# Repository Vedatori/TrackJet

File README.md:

# TrackJet (cz)
TrackJet je otevřená platforma robotického vozidla vyvinutá pro [Robotický tábor 2021](http://wp.vedatori.com/pobytove-tabory/) organizovaný spolkem [Vědátoři](http://wp.vedatori.com/). Jedná se o nástupní verzi vozidla [TrackRay](https://github.com/vedatori/TrackRay), ve které byly vylepšeny jeho terénní schopnosti a přidány nové funkcionality. Byla redesignována mehanická konstrukce i řídicí elektronika, pro kterou byl vyvinut odpovídající software. 

Hlavní mechanickou částí je 3D tištěné šasi, které je doplněno dalšími 3D tištěnými díly. Plošné díly jsou laserem vyřezány z překližky. Spojování je prováděno především šrouby M3. Je použito minimum lepených spojů tak, aby bylo možné vrátit jakýkoliv krok při stavbě. Obsahuje zadní pohonná kola a na každé straně dále tři kola pro vedení pásu. Všechna kola jsou uložena pevně. Pásy jsou vytištěny na 3D tiskárně tak, aby se již při tisku vytvořilo kloubové spojení jednotlivých segmentů, což vede ke snížení času potřebného pro stavbu.

Veškerá elektronika je umístěna na jedné DPS. Ze spodní strany je připevněn zdroj energie - akumulátor 18650. Jeho nabíjení je řešeno na DPS, pro nabití není nutné ho vyjmout. Robota řídí ESP32 připájené přímo do DPS. Pro orientaci v prostoru robot využívá snímání pohybu pásů pomocí optických enkodérů a senzoru LiDAR umístěného na otočné konzoli. Vstupy od uživatele je možné zadat pomocí rotačního enkodéru, potenciometru a tlačítka, výstupy jsou zobrazeny na LED matici, bzučákem nebo jiných LED. Programování a nabíjení robota je prováděno přes USB-C.

Software je připraven na výuku programování. Tomu je přizpůsobena knihovna, pomocí které uživatelé jednoduše ovládají periferie robota bez nutnosti nízkoúrovňového programování jednotlivých částí. Pro výuku programování je připraven také návod popisující jednotlivé funkce a příklady jejich použití. Vše bylo navrženo s důrazem na rozvoj schopností algoritmizace a programování účastníků.
Součástí softwarového balíku je i kompletní program pro dálkové ovládání přes WiFi. Vozidlo umožňuje komunikaci jak přes vlastní WiFi, tak přihlášení k již existující síti. To mu umožňuje jízdu i v širém prostoru. TrackJet můžete vidět v akci v [tomto videu](https://www.youtube.com/watch?v=zHig3jCnhBY).

Při stavbě TrackJet postupujte podle připravených návodů v následujícím pořadí:
1. [Návod pro mechaniku](https://github.com/vedatori/TrackJet/blob/main/Manuals/TrackJet_mechanics_cz.md)
1. [Návod pro elektroniku](https://github.com/vedatori/TrackJet/blob/main/Manuals/TrackJet_electronics_cz.md)
1. [Návod pro programování](https://github.com/vedatori/TrackJet/blob/main/Manuals/TrackJet_programming_cz.md)

## Licence
* Obsah tohoto repozitáře mimo složku *Software* je sdílen pod licencí [Attribution-NonCommercial-ShareAlike 4.0 International (CC BY-NC-SA 4.0)](https://creativecommons.org/licenses/by-nc-sa/4.0/).
* Obsah složky *Software* je sdílen pod licencí [GNU Lesser General Public License v3.0](https://www.gnu.org/licenses/lgpl-3.0.en.html).

# TrackJet (en)

TrackJet is an open-source robotic vehicle platform developed for the [Robotic camp 2021 (cz)](http://wp.vedatori.com/pobytove-tabory/) organized by [Vědátoři (cz)](http://wp.vedatori.com/) society. It is a succesor of [TrackRay](https://github.com/vedatori/TrackRay) robotic vehicle. TrackJet introduces enhanced terrain abilities and new functionalities. Mechanical parts, electronics and software were redesigned.

TrackJet consists of a main 3D printed part - chassis, several other 3D printed parts and laser cut plywood parts. M3 bolts are used in the assembly process, which grants the possibility to undo every step in case of assembly error. Rear propulsion wheel and three guiding wheels are placed on every side of the vehicle. Tracks are designed to be 3D printed in one piece with joints between segments which minimizes assembly time.

All electronic components are placed on a single PCB. This board contains 18650 battery and a charger circuit. Therefore, it is not needed to take the battery out in order to charge it. ESP32 soldered to the PCB is used for peripherals control and WiFi connectivity. TrackJet finds its orientation in space using LiDAR sensor and optical encoders. User inputs can be made using rotary encoder, potentiometer and a button. LED matrix, buzzer and other LEDs are used for communication with user. Vehicle is programmed and charged via USB-C.

Electronics and software is designed for programming education. TrackJet contains a library which allows easy peripherals control without the need of low-level programming abilities. Repository contains programming manual (in czcech language) with description of commands and examples. WiFi remote control is a part of the software pack in this repository. ESP32 can be connected to external WiFi or it can create its own network so it is possible to drive outdoors without network coverage. You can see TrackJet in action in [this video](https://www.youtube.com/watch?v=zHig3jCnhBY).

In the build of the TrackJet proceed according to the prepared manuals in the following order:
1. [Mechanics manual](https://github.com/vedatori/TrackJet/blob/main/Manuals/TrackJet_mechanics_cz.md)
1. [Electronics manual](https://github.com/vedatori/TrackJet/blob/main/Manuals/TrackJet_electronics_cz.md)
1. [Programming manual](https://github.com/vedatori/TrackJet/blob/main/Manuals/TrackJet_programming_cz.md)

## License
* The contents of this repository excluding folder *Software* is shared under license [Attribution-NonCommercial-ShareAlike 4.0 International (CC BY-NC-SA 4.0)](https://creativecommons.org/licenses/by-nc-sa/4.0/).
* The contents of the folder *Software* is shared under license [GNU Lesser General Public License v3.0](https://www.gnu.org/licenses/lgpl-3.0.en.html).

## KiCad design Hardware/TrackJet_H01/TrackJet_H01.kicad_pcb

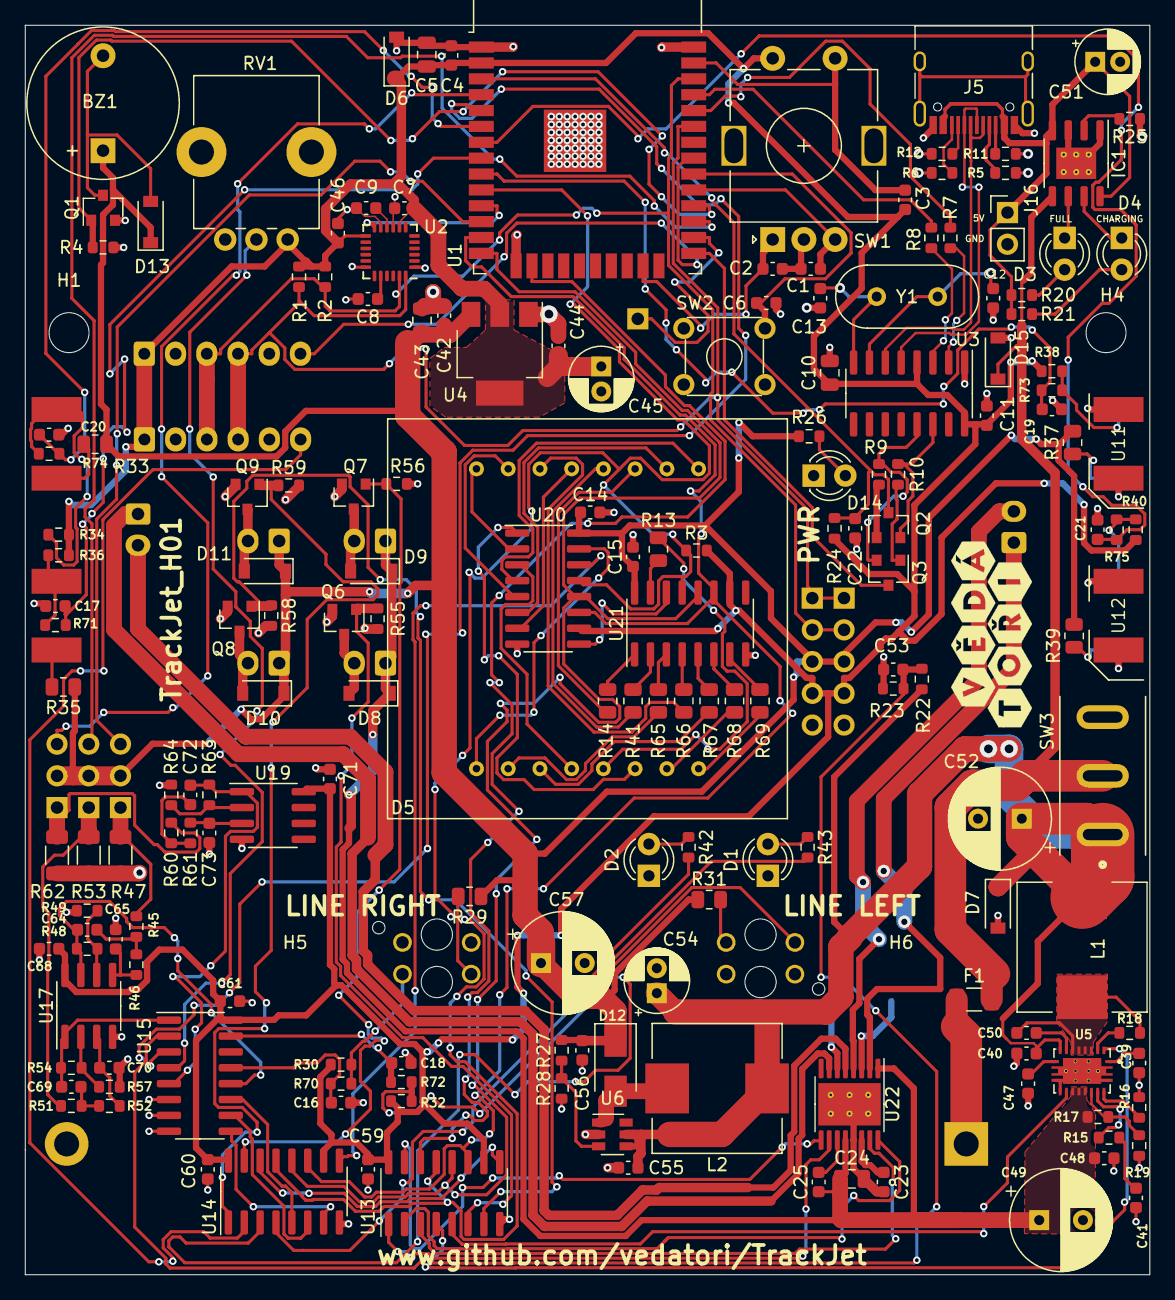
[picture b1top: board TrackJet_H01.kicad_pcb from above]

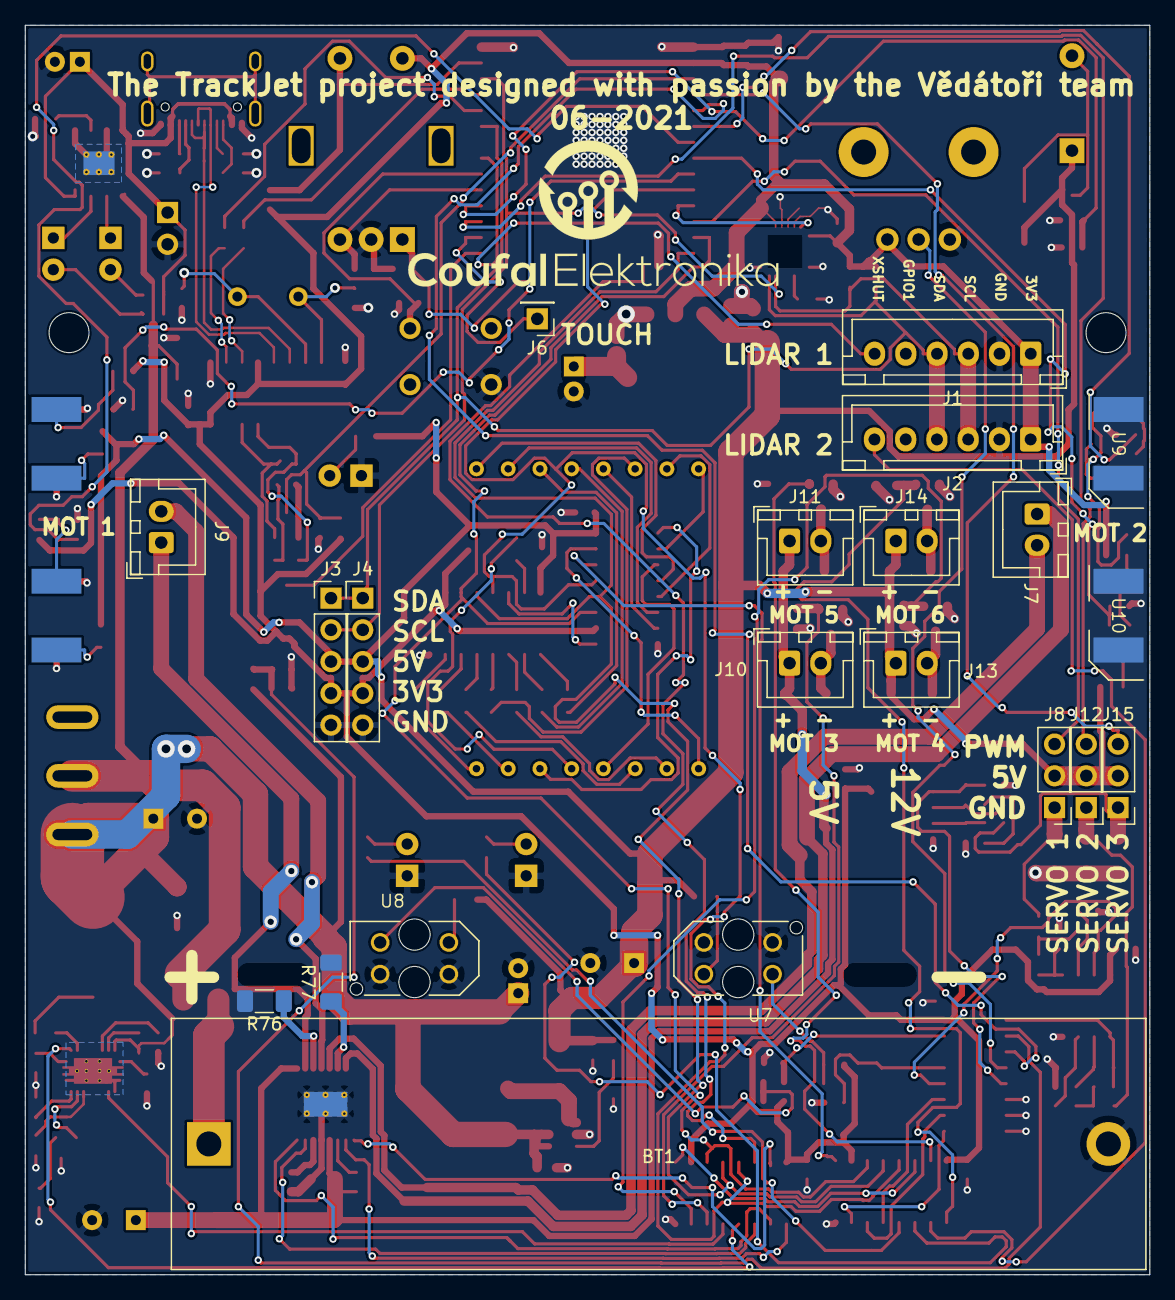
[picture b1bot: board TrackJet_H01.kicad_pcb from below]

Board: 2 copper layers, 90.0 x 100.0 mm, 205 parts (22 on the bottom side), 156 nets.

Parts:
BT1: 18650; BatteryHolder_MPD_BH-18650-PC2_NoHoles
BZ1: Buzzer; Buzzer_12x9.5RM7.6
C1, C2, C3, C4, C6, C7, C9, C11, C14, C15, C16, C17, C18, C19, C20, C21, C40, C42, C44, C46, C47, C48, C50, C53, C55, C56, C59, C60, C61, C68, C71: 100n; C_0603_1608Metric
C5, C10, C24, C43: 10u; C_0805_2012Metric
C8: 2n2; C_0603_1608Metric
C12, C13: 22p; C_0603_1608Metric
C22, C39: 1u; C_0603_1608Metric
C23: 2u2; C_0603_1608Metric
C25: 10n; C_0603_1608Metric
C41: 1n; C_0603_1608Metric
C45, C51, C54: 100u; CP_Radial_D5.0mm_P2.00mm
C49, C52, C57: 1000u 16V; CP_Radial_D8.0mm_P3.50mm
C64, C65, C69, C70, C72, C73: 220n; C_0603_1608Metric
D1, D2: LED; LED_D3.0mm
D3, D14: LED_GREEN; LED_D3.0mm
D4: LED_RED; LED_D3.0mm
D5: KYX-1088AS
D6, D7, D8, D9, D10, D11, D13, D15: B5819W; D_SOD-123
D12: SS34; D_SMA
F1: Fuse 15A; Fuse_1206_3216Metric
G1: LOGO; Coufal_elektronika_text_30x13mm
G2: LOGO; Vedatori_15mm
H1, H4: MountingHole; MountingHole_3.2mm_M3
H5, H6: MountingHole; ZIP_Tie_Slot_Hole
IC1: TP4056; SOIC-8-1EP_3.9x4.9mm_P1.27mm_EP2.514x3.2mm_ThermalVias
J1, J2: Conn_01x06_Female; JST_XH_B6B-XH-A_1x06_P2.50mm_Vertical
J3, J4: Conn_01x05_Male; PinHeader_1x05_P2.54mm_Vertical
J5: TYPE-C-31-M-12; USB_C_Receptacle_HRO_TYPE-C-31-M-12
J6: Conn_01x01_Male; PinHeader_1x01_P2.54mm_Vertical
J7, J9, J10, J11, J13, J14: Conn_01x02; JST_XH_B2B-XH-A_1x02_P2.50mm_Vertical
J8, J12, J15: Conn_01x03_Male; PinHeader_1x03_P2.54mm_Vertical
J16: Conn_01x02_Male; PinHeader_1x02_P2.54mm_Vertical
L1: 2u2; L_Wuerth_HCI-1040
L2: 22uH; L_Wuerth_HCI-1040
Q1: 2N7002; SOT-23
Q2, Q3: S8050; SOT-23
Q6, Q7, Q8, Q9: AO3400A; SOT-23
R1, R2: 2K2; R_0603_1608Metric
R3, R4, R24, R55, R56, R58, R59: 10K; R_0603_1608Metric
R5, R6, R11, R12: 5K1; R_0603_1608Metric
R7, R8: 470R; R_0603_1608Metric
R9, R10: 12K; R_0603_1608Metric
R13, R14, R29, R31, R33, R35, R37, R39, R41, R65, R66, R67, R68, R69: 100R; R_0805_2012Metric
R15: 24K; R_0603_1608Metric
R16: 150K; R_0603_1608Metric
R17: 200K; R_0603_1608Metric
R18: 240K; R_0603_1608Metric
R19, R28: 30K; R_0603_1608Metric
R20, R21, R26, R30, R32, R34, R36, R38, R40: 1K; R_0603_1608Metric
R22, R46, R52, R61: 1M; R_0603_1608Metric
R23: 3M; R_0603_1608Metric
R25: 1K2; R_0603_1608Metric
R27: 220K; R_0603_1608Metric
R42, R43: 220R; R_0603_1608Metric
R45, R51, R60, R70, R71, R72, R73, R74, R75: 22K; R_0603_1608Metric
R47, R53, R62: 0R1; R_1206_3216Metric
R48, R54, R63: 47K; R_0603_1608Metric
R49, R57, R64: 1K5; R_0603_1608Metric
R76, R77: R; R_1206_3216Metric_Pad1.30x1.75mm_HandSolder
RV1: R_POT; Potentiometer_Alps_RK09K_Single_Vertical
SW1: Rotary_Encoder_Switch; RotaryEncoder_Alps_EC11E-Switch_Vertical_H20mm
SW2: SW_DPST; SW_TH_Tactile_Omron_B3F-10xx
SW3: MT-102; TE_A101SYCQ04
U1: ESP32-WROOM-32D; ESP32-WROOM-32
U2: MPU-6050; InvenSense_QFN-24_4x4mm_P0.5mm
U3: CH340G; SOIC-16_3.9x9.9mm_P1.27mm
U4: AMS1117-3.3; SOT-223-3_TabPin2
U5: TPS61088RHLR; IC_TPS61088RHLR
U6: MT3608; SOT-23-6
U7, U8: TCRT5000
U9, U10, U11, U12: TCRT5000; TCRT5000_SMD
U13, U14, U20, U21: 74HC595; SOIC-16_3.9x9.9mm_P1.27mm
U15: CD4051B; SOIC-16_3.9x9.9mm_P1.27mm
U17, U19: LM358; SOIC-8_3.9x4.9mm_P1.27mm
U22: DRV8833PWP; HTSSOP-16-1EP_4.4x5mm_P0.65mm_EP3.4x5mm_Mask2.46x2.31mm_The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
Y1: 12MHz; Crystal_HC49-4H_Vertical

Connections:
+3V3: C3.2, C4.1, C5.1, C7.1, C10.1, C11.1, C44.1, C45.1, C46.1, C59.1, C60.1, C61.1, C68.1, C71.1, D6.1, J1.1, J2.1, J3.4, J4.4, R1.1, R2.1, R3.1, R24.1, R30.1, R32.1, R34.1, R36.1, R38.1, R40.1, RV1.1, SW1.S2, U1.2, U2.8, U2.13, U3.4, U3.16, U4.2, U13.10, U13.16, U14.10, U14.16, U15.16, U17.8, U19.8, U20.10, U21.10
+5V: BZ1.1, C14.1, C15.1, C42.1, C43.1, C56.1, C57.1, D10.1, D11.1, D12.1, D13.1, J3.3, J4.3, J8.2, J12.2, J13.1, J14.1, J15.2, R26.1, R27.2, R29.1, R31.1, R33.1, R35.1, R37.1, R39.1, U4.3, U20.16, U21.16
+5VP: C51.1, IC1.4, IC1.8, J5.A4, J5.A9, J5.B4, J5.B9, J16.1, R20.1, R21.1
+12V: C24.1, C25.1, C48.1, C49.1, D8.1, D9.1, J10.1, J11.1, R17.2, U5.14, U5.15, U5.16, U22.1, U22.12
+BATT: C40.1, C52.1, C54.1, C55.1, D7.1, L1.1, L2.1, R22.1, SW3.1, U5.9, U6.4, U6.5
/Encoders/ENCODER2: C17.1, R71.1, U1.8
/Encoders/ENCODER4: C19.1, R73.1, U1.9
/Encoders/ENCODER5: C20.1, R74.1, U1.6
/Encoders/ENCODER6: C21.1, R75.1, U1.7
/Gyro/MPU-6050_INT: U1.11, U2.12
/Motors/DC_MOT1_12V: Q6.1, R55.1, U13.6
/Motors/DC_MOT2_5V: Q8.1, R58.1, U13.7
/Motors/DC_MOT3_12V: Q7.1, R56.1, U14.15
/Motors/DC_MOT4_5V: Q9.1, R59.1, U14.1
/Motors/MOTA_IN1: U13.15, U22.9
/Motors/MOTA_IN2: U13.1, U22.10
/Motors/MOTB_IN1: U13.2, U22.16
/Motors/MOTB_IN2: U13.3, U22.15
/Motors/SERVO1_CTRL: J8.3, U1.12
/Motors/SERVO2_CTRL: J12.3, U1.27
/Motors/SERVO3_CTRL: J15.3, U1.4
/Mux Demux Matrix/Analog_IN_1: C16.1, R70.1, U15.13
/Mux Demux Matrix/Analog_IN_3: C18.1, R72.1, U15.15
/Mux Demux Matrix/Analog_IN_4: C64.1, R48.1, U15.12, U17.7
/Mux Demux Matrix/Analog_IN_5: C69.1, R54.1, U15.1, U17.1
/Mux Demux Matrix/Analog_IN_6: C72.1, R63.1, U15.5, U19.1
/Mux Demux Matrix/Analog_IN_7: C53.1, R22.2, R23.1, U15.2
/Mux Demux Matrix/Analog_MUX: U1.5, U15.3
/Mux Demux Matrix/REG_CLK: U1.13, U13.11, U14.11, U20.11, U21.11
/Mux Demux Matrix/REG_DAT: U1.16, U13.14
/Mux Demux Matrix/REG_LAT: U1.14, U13.12, U14.12, U20.12, U21.12
/Mux Demux Matrix/REG_OE: R3.2, U1.10, U13.13, U14.13, U20.13, U21.13
/Mux Demux Matrix/REG_OUT_11: J2.6, U14.2
/Power/12V_ENABLE: U5.2, U13.4
/Power/12V_MODE: U5.13, U13.5
/USB/D+: J5.A6, J5.B6, U3.5
/USB/D-: J5.A7, J5.B7, U3.6
/USB/ESP_GPIO0: Q3.3, U1.25
/USB/ESP_RST: C22.2, Q2.3, R24.2, U1.3
/USB/ESP_RX: R7.1, U1.34
/USB/ESP_TX: R8.1, U1.35
BUTTON: C6.2, SW2.2, U1.30
BUZZER: Q1.1, R4.1, U1.28
ENC_A: C2.1, SW1.A, U1.23
ENC_B: C1.2, SW1.B, U1.29
ENC_SW: C3.1, SW1.S1, U1.37
GND: BT1.2, C1.1, C2.2, C4.2, C5.2, C6.1, C7.2, C8.2, C9.2, C10.2, C11.2, C12.2, C13.2, C14.2, C15.2, C16.2, C17.2, C18.2, C19.2, C20.2, C21.2, C22.1, C23.2, C24.2, C39.1, C40.2, C41.1, C42.2, C43.2, C44.2, C45.2, C46.2, C47.2, C48.2, C49.2, C51.2, C52.2, C53.2, C54.2, C55.2, C56.2, C57.2, C59.2, C60.2, C61.2, C65.1, C68.2, C70.1, C71.2, C73.1, D1.1, D2.1, D6.2, D7.2, D14.1, D15.2, IC1.1, IC1.3, IC1.9, J1.2, J2.2, J3.5, J4.5, J5.A1, J5.A12, J5.B1, J5.B12, J16.2, Q1.2, Q6.2, Q7.2, Q8.2, Q9.2, R4.2, R5.1, R6.1, R11.2, R12.2, R16.1, R19.1, R23.2, R25.1, R28.1, R47.2, R49.1, R53.2, R55.2, R56.2, R57.1, R58.2, R59.2, R62.2, R64.1, R76.2, R77.2, RV1.3, SW1.C, SW2.3, U1.1, U1.15, U1.38, U1.39, U2.1, U2.9, U2.11, U2.18, U3.1, U4.1, U5.11, U5.12, U5.20, U5.21, U5.22, U5.23, U5.24, U5.25, U5.26, U5.27, U5.28, U5.29, U6.2, U7.2, U7.4, U8.2, U8.4, U9.2, U9.4, U10.2, U10.4, U11.2, U11.4, U12.2, U12.4, U13.8, U14.8, U15.6, U15.7, U15.8, U17.4, U19.4, U20.8, U21.8, U22.13, U22.17
unnamed: BT1.1, F1.2
unnamed: BZ1.2, D13.2, Q1.3
unnamed: C8.1, U2.20
unnamed: C9.1, U2.10
unnamed: C12.1, U3.7, Y1.1
unnamed: C13.1, U3.8, Y1.2
unnamed: C23.1, U22.14
unnamed: C25.2, U22.11
unnamed: C39.2, U5.1
unnamed: C41.2, R15.1
unnamed: C47.1, U5.10
unnamed: C50.1, U5.8
unnamed: C50.2, L1.2, R18.2, U5.4, U5.5, U5.6, U5.7
unnamed: C64.2, R45.1, R46.2
unnamed: C65.2, R46.1, U17.5
unnamed: C69.2, R51.1, R52.2
unnamed: C70.2, R52.1, U17.3
unnamed: C72.2, R60.1, R61.2
unnamed: C73.2, R61.1, U19.3
unnamed: D1.2, R43.1
unnamed: D2.2, R42.1
unnamed: D3.1, IC1.6
unnamed: D3.2, R20.2
unnamed: D4.1, IC1.7
unnamed: D4.2, R21.2
unnamed: D5.1, U20.4
unnamed: D5.2, U20.6
unnamed: D5.3, R14.2
unnamed: D5.4, R41.2
unnamed: D5.5, U20.7
unnamed: D5.6, R66.2
unnamed: D5.7, U20.5
unnamed: D5.8, U20.2
unnamed: D5.9, U20.15
unnamed: D5.10, R65.2
unnamed: D5.11, R67.2
unnamed: D5.12, U20.3
unnamed: D5.13, R13.2
unnamed: D5.14, U20.1
unnamed: D5.15, R68.2
unnamed: D5.16, R69.2
unnamed: D8.2, J10.2, Q6.3
unnamed: D9.2, J11.2, Q7.3
unnamed: D10.2, J13.2, Q8.3
unnamed: D11.2, J14.2, Q9.3
unnamed: D12.2, L2.2, U6.1
unnamed: D14.2, R26.2
unnamed: D15.1, F1.1, IC1.5, SW3.2
unnamed: IC1.2, R25.2
unnamed: J1.6, U1.31
unnamed: J5.A5, R5.2
unnamed: J5.A8, R12.1
unnamed: J5.B5, R6.2
unnamed: J5.B8, R11.1
unnamed: J6.1, U1.26
unnamed: J7.1, U22.7
unnamed: J7.2, U22.5
unnamed: J8.1, R45.2, R47.1
unnamed: J9.1, U22.2
unnamed: J9.2, U22.4
unnamed: J12.1, R51.2, R53.1
unnamed: J15.1, R60.2, R62.1
unnamed: Q2.1, R9.1
unnamed: Q2.2, R10.2, U3.14
unnamed: Q3.1, R10.1
unnamed: Q3.2, R9.2, U3.13
unnamed: R7.2, U3.2
unnamed: R8.2, U3.3
unnamed: R13.1, U21.15
unnamed: R14.1, U21.1
unnamed: R15.2, U5.18
unnamed: R16.2, U5.19
unnamed: R17.1, R19.2, U5.17
unnamed: R18.1, U5.3
unnamed: R27.1, R28.2, U6.3
unnamed: R29.2, U7.1
unnamed: R30.2, R70.2, U7.3
unnamed: R31.2, U8.1
unnamed: R32.2, R72.2, U8.3
unnamed: R33.2, U9.1
unnamed: R34.2, R74.2, U9.3
unnamed: R35.2, U10.1
unnamed: R36.2, R71.2, U10.3
unnamed: R37.2, U11.1
unnamed: R38.2, R73.2, U11.3
unnamed: R39.2, U12.1
unnamed: R40.2, R75.2, U12.3
unnamed: R41.1, U21.2
unnamed: R42.2, U14.3
unnamed: R43.2, U14.4
unnamed: R48.2, R49.2, U17.6
unnamed: R54.2, R57.2, U17.2
unnamed: R63.2, R64.2, U19.2
unnamed: R65.1, U21.3
unnamed: R66.1, U21.4
unnamed: R67.1, U21.5
unnamed: R68.1, U21.6
unnamed: R69.1, U21.7
unnamed: R76.1, U22.3
unnamed: R77.1, U22.6
unnamed: U13.9, U14.14
unnamed: U14.5, U15.11
unnamed: U14.6, U15.10
unnamed: U14.7, U15.9
unnamed: U14.9, U20.14
unnamed: U20.9, U21.14
POT: RV1.2, U15.4
SCL: J1.3, J2.3, J3.2, J4.2, R2.2, U1.36, U2.23
SDA: J1.4, J2.4, J3.1, J4.1, R1.2, U1.33, U2.24

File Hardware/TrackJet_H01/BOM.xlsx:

Comment | Designator | Footprint | LCSC
22p | C12,C13 | Capacitor_SMD:C_0603_1608Metric | C1653
1u | C22,C39 | Capacitor_SMD:C_0603_1608Metric | C15849
2u2 | C23 | Capacitor_SMD:C_0603_1608Metric | C23630
10n | C25 | Capacitor_SMD:C_0603_1608Metric | C57112
100n | C1,C2,C3,C4,C6,C7,C9,C11,C14,C15,C16,C17,C18,C19,C20,C21,C40,C42,C44,C46,C47,C4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 | Capacitor_SMD:C_0603_1608Metric | C14663
1n | C41 | Capacitor_SMD:C_0603_1608Metric | C1588
10u | C5,C10,C24,C43 | Capacitor_SMD:C_0805_2012Metric | C15850
220n | C64,C65,C69,C70,C72,C73 | Capacitor_SMD:C_0603_1608Metric | C21120
2n2 | C8 | Capacitor_SMD:C_0603_1608Metric | C1604
SS34 | D12 | Diode_SMD:D_SMA | C8678
B5819W | D6,D7,D8,D9,D10,D11,D13,D15 | Diode_SMD:D_SOD-123 | C8598
Fuse 15A | F1 | Fuse:Fuse_1206_3216Metric | C182976
TP4056 | IC1 | Package_SO:SOIC-8-1EP_3.9x4.9mm_P1.27mm_EP2.514x3.2mm_ThermalVias | C382139
TYPE-C-31-M-12 | J5 | Connector_USB:USB_C_Receptacle_HRO_TYPE-C-31-M-12 | C165948
2u2 | L1 | Inductor_SMD:L_Wuerth_HCI-1040 | C149550
22uH | L2 | Inductor_SMD:L_Wuerth_HCI-1040 | C182173
2N7002 | Q1 | Package_TO_SOT_SMD:SOT-23 | C8545
S8050 | Q2,Q3 | Package_TO_SOT_SMD:SOT-23 | C2146
AO3400A | Q6,Q7,Q8,Q9 | Package_TO_SOT_SMD:SOT-23 | C20917
12K | R9,R10 | Resistor_SMD:R_0603_1608Metric | C22790
5K1 | R5,R6,R11,R12 | Resistor_SMD:R_0603_1608Metric | C23186
24K | R15 | Resistor_SMD:R_0603_1608Metric | C23352
150K | R16 | Resistor_SMD:R_0603_1608Metric | C22807
200K | R17 | Resistor_SMD:R_0603_1608Metric | C25811
240K | R18 | Resistor_SMD:R_0603_1608Metric | C4197
30K | R19,R28 | Resistor_SMD:R_0603_1608Metric | C22984
2K2 | R1,R2 | Resistor_SMD:R_0603_1608Metric | C4190
1K | R20,R21,R26,R30,R32,R34,R36,R38,R40 | Resistor_SMD:R_0603_1608Metric | C21190
1M | R22,R46,R52,R61 | Resistor_SMD:R_0603_1608Metric | C22935
3M | R23 | Resistor_SMD:R_0603_1608Metric | C23156
1K2 | R25 | Resistor_SMD:R_0603_1608Metric | C22765
220K | R27 | Resistor_SMD:R_0603_1608Metric | C22961
100R | R13,R14,R29,R31,R33,R35,R37,R39,R41,R65,R66,R67,R68,R69 | Resistor_SMD:R_0805_2012Metric | C17408
10K | R3,R4,R24,R55,R56,R58,R59 | Resistor_SMD:R_0603_1608Metric | C25804
220R | R42,R43 | Resistor_SMD:R_0603_1608Metric | C22962
0R1 | R47,R53,R62 | Resistor_SMD:R_1206_3216Metric | C25334
47K | R48,R54,R63 | Resistor_SMD:R_0603_1608Metric | C25819
1K5 | R49,R57,R64 | Resistor_SMD:R_0603_1608Metric | C22843
22K | R45,R51,R60,R70,R71,R72,R73,R74,R75 | Resistor_SMD:R_0603_1608Metric | C31850
470R | R7,R8 | Resistor_SMD:R_0603_1608Metric | C23179
ESP32-WROOM-32D | U1 | RF_Module:ESP32-WROOM-32 | C473012
74HC595 | U13,U14,U20,U21 | Package_SO:SOIC-16_3.9x9.9mm_P1.27mm | C5947
CD4051B | U15 | Package_SO:SOIC-16_3.9x9.9mm_P1.27mm | C21379
LM358 | U17,U19 | Package_SO:SOIC-8_3.9x4.9mm_P1.27mm | C7950
MPU-6050 | U2 | Sensor_Motion:InvenSense_QFN-24_4x4mm_P0.5mm | C24112
CH340G | U3 | Package_SO:SOIC-16_3.9x9.9mm_P1.27mm | C14267
AMS1117-3.3 | U4 | Package_TO_SOT_SMD:SOT-223-3_TabPin2 | C6186
TPS61088RHLR | U5 | Sergej_Library:IC_TPS61088RHLR | C87357
MT3608 | U6 | Package_TO_SOT_SMD:SOT-23-6 | C84817

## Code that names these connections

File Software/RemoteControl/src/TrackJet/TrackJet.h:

#pragma once

#include <Arduino.h>
#include <Wire.h>
#include "Preferences.h"

#include "VL53L0X.h"
#include "MPU6050_light.h"

#include "SerialPWM.h"
#include "WiFiCaptain.h"
#include "QuadEncoder.h"
#include "SemiIntelligentServo.h"
#include "Music.h"


namespace TJ {

const uint16_t PWM_FREQUENCY = 1000;

const uint8_t REG_DAT = 13;
const uint8_t REG_CLK = 14;
const uint8_t REG_LATCH = 12;
const uint8_t REG_OE = 25;
const uint8_t I2C_SDA = 21;
const uint8_t I2C_SCL = 22;

const uint8_t ENC_A = 15;
const uint8_t ENC_B = 5;
const uint8_t ENC_SW = 23;
const uint8_t BUTTON = 18;
const uint8_t LIDAR = 19;
const uint8_t BUZZER = 17;
const uint8_t ADC_MUX = 39;
const adc1_channel_t ADC_CH_COM = ADC1_CHANNEL_3;
const adc1_channel_t ADC_CH_ENC_FR = ADC1_CHANNEL_4;
const adc1_channel_t ADC_CH_ENC_RL = ADC1_CHANNEL_5;
const adc1_channel_t ADC_CH_ENC_RR = ADC1_CHANNEL_6;
const adc1_channel_t ADC_CH_ENC_FL = ADC1_CHANNEL_7;

#define SERVO_COUNT 3
const uint8_t SERVO[SERVO_COUNT] = {27, 16, 36};
const uint8_t SERVO_CHANNEL[SERVO_COUNT] = {0, 1, 2};
const uint8_t BUZZER_CHANNEL = 3;

const float MOTOR_SPEED_FILTER_UPDATE_COEF = 0.15;
const float BATT_VOLTAGE_UPDATE_COEF = 0.05;
const float BATT_VOLTAGE_CUTOFF = 3.4;    // [V]
const float BATT_VOLTAGE_RESET = 3.6;     // [V]

const uint16_t encThresholdInit = 1600;

const uint8_t FREQ_PWM_THRESHOLD = 40;
const uint16_t controlPeriod = 10;  // [ms]
const char STORAGE_NAMESPACE[] = "TrackJet";
const uint16_t communicationTimeout = 1000;
const uint16_t lettersSwapTimeout = 500;
const uint16_t lettersBlankTimeout = 50;
const uint16_t lettersSweepTimeout =  100;

extern SerialPWM serialPWM;
extern QuadEncoder quadEnc;
extern SemiIntelligentServo servo[SERVO_COUNT];
extern MPU6050 mpu;
extern VL53L0X lidar;
void updatePWM(void * param);
void updateEnc(void * param);
uint8_t encGetState(uint8_t encID);
void handleRot();
void handleSW();
}

enum shiftRegPins {
    MOT1A, MOT1B, MOT2A, MOT2B, STEP_EN, STEP_MODE, MOT3, MOT4, MOT5, MOT6, 
    XSHUT, LED2, LED1, MUXA, MUXB, MUXC
};

enum adcMuxPins {
    LINE_SENSOR_RIGHT, NC, LINE_SENSOR_LEFT, SERVO_CURR_1, SERVO_CURR_2, SERVO_CURR_3, BAT_VOLT, POTENTIOMETER
};

class TrackJetClass {
    bool beginCalled = false;
    int8_t motorsSpeed[2];
    //float motorsSpeedFiltered[2];
    uint8_t gyroStatus = 0; // 0-disabled, 1-running, 2-calibrating
    float gyroYPR[3];
    float gyroOffsets[3];
    float accelOffsets[3];
    uint16_t analogReadData[8];
    uint8_t lidarStatus = 0;    // 0-disabled, 1-running
    uint16_t lidarDist = 0;
    Preferences preferences;
    uint32_t prevCommunicationTime = 0;
    bool connectionEnabled = false;
    bool connectionActive = false;
    String displayTextBuffer;
    float battVoltageFiltered = 3.7;
    float battPercentFiltered = 50;
    bool battCutoff = false;    // false-high V., true-low V.

    bool melodyPlaying = false;
    bool melodyPause = false;
    int melodyTempo = 180;
    const int * melody;
    int melodythisNote = 0;
    int melodySize = 0;
    unsigned long melodyLastMillis = 0;

public:
    uint16_t encThreshold[4];   // 0-FL, 1-RL, 2-FR, 3-RR
    int16_t encSteps[2];    // 0-Left, 1-right
    TrackJetClass();
    void begin();

    bool buttonRead();
    uint16_t potentiometerRead();   // 0-100
    bool encoderReadButton();
    bool encoderReadButtonPulse();
    int16_t encoderRead();
    void encoderReset();

    void motorSetSpeed(const int8_t index, int8_t speed);
    void motorsUpdateSpeed();
    void controlMovement(const int8_t joystickX, const int8_t joystickY);

    int16_t encoderGetSteps(uint8_t encID);
    float encoderGetDistance(uint8_t encID);
    float encoderGetSpeed(uint8_t encID);
    void encoderDistReset(uint8_t encID);

    void servoSetPosition(uint8_t servoID, float position);     // servoID 1, 2, 3; position 0-180 [°]
    void servoSetSpeed(uint8_t servoID, float speed);    // speed 0-600 [°/s]
    float servoGetPosition(uint8_t servoID);
    bool servoMoving(uint8_t servoID);

    void soundTone(float freq = 1000);
    void soundEnd();
    void playMelody(const int * aMelody, const int size, const int tempo = 180);
    void stopMelody();
    void handleMelody();

    uint8_t gyroGetStatus();
    float gyroAngleYPR(uint8_t index) ;
    void gyroCalibrate();
    void gyroUpdate();
    void printOffsets() {
        printf("offsets: %f %f %f %f %f %f\n", gyroOffsets[0], gyroOffsets[1], gyroOffsets[2], accelOffsets[0], accelOffsets[1], accelOffsets[2]);
    }

    void updateAnalogMux();

    float battVolt();
    float battPercentCalc(float voltage);
    uint8_t battPercent();
    void handleLowBatt();

    uint16_t lineRead(uint8_t index);

    uint16_t lidarDistance();
    void lidarUpdate();

    void ledWrite(uint8_t id, bool state);
    void ledWriteAnalog(uint8_t id, uint8_t brightness);    // brightness 0-100

    void displaySingle(uint8_t row, uint8_t col, bool state);
    void displaySingleAnalog(uint8_t row, uint8_t col, int8_t brightness);   // brightness 0-12
    void displayAll(int8_t value);
    void display(uint8_t state[][DISP_COLS]);
    void displayDigit(const uint8_t digit);
    void displayChar(const char letter, int8_t sweepRight = 0, int8_t sweepDown = 0);
    void displayText(String text = "", bool sweep = true);
    bool displayIsBusy();

    void startWiFiCaptain(String name="", String password="");
    void checkConnection();
    String commandGet();
    String commandGetIndexed(uint8_t index);
    void commandClear();
    void internCommandHandle();
    void commandSend(String type, String text);
    void commandDisp(String text);
    void sendStatus();

    void encoderCalibrate(uint16_t duration);
};

extern TrackJetClass TrackJet;

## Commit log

2021-03-19 Initial commit. Repository upgrade.
2021-03-19 Added first Hardware prototype.
2021-03-22 Routed PCB
2021-03-23 Final changes made to Sergej_H00, exported gerbers
2021-03-23 updated schematics - part values and LCSC numbers
2021-04-22 Notes for H01 and electronics analysis.
2021-04-29 To do list for next HW version
2021-04-29 exported layout in PDF
2021-05-02 Started testing I2S parallel
2021-05-07 Removed "data pins" universality
2021-05-08 Functional remote control demo.
2021-05-14 Removed [ ] pwm operator.
2021-05-15 ShiftReg pin mapping and Handling OE pin in class.
2021-05-16 removed std_vector and initializer list, output indexing from 0
2021-05-17 Displaying any matrix setting defined in 2d array
2021-05-17 Fixed diplay orientation. Simple serialPWM disp api.
2021-05-17 Adding disp api array bound security.
2021-05-17 Renamed everywhere to TrackJet.
2021-05-17 Integrated SerialPWM into RemoteControl.
2021-05-18 Rotated disp orientation to be viewed from front. Displaying texts.
2021-05-18 Added quadratic encoder.
2021-05-19 Refactoring TJ function names, shift reg output pins ordering.
2021-05-22 Controlling servos (+remotely through commands).
2021-05-22 Created TrackJet_H01
    Created TrackJet_H01 KiCad project and ported H00 version. Updated To-Do list. Renamed all files to TrackJet_Hxx except Sergej Library for compatibiliti with used symbols and footprints.
2021-05-22 Introduced servo class.
2021-05-22 Added speed adjustment of servos.
2021-05-23 Added MPU6050_light and reading YPR, calibrating and storing gyro calibration.
2021-05-23 Indicating tilt angles on display.
2021-05-23 Storing accelerometer calibration.
2021-05-24 Added lidar.
2021-05-29 Reading analog from mux in single-connection mode.
2021-06-11 Updated H01 PCB
2021-06-13 Updated H01
2021-06-13 Lidar measurements with defined period
2021-06-14 H01 update
2021-06-14 Exported H01 manufactuirng data
2021-06-14 Updated manufacturing data
2021-07-11 Transition to H01. Added tracks encoder demo. Remove servo steady movement because of a bug.
2021-07-30 Mechanics manual cz, 1st version
2021-07-31 Mechanics manual cz, revision
2021-08-08 Fixed lib naming issues with mac. Pinned updatePWM task to core 1 (same as main)
2021-08-08 Review návodu pro mechaniku.
2021-08-08 Fixed WiFi softAp name conflict. Removed default password.
2021-08-10 Electronics manual cz, 1st version
2021-08-10 Electronics manual cz, revision
2021-08-10 Reading analog mux inputs. Monitoring battery voltage.
2021-08-10 Gyro preferences loading only when gyro connected.
2021-08-11 programing manual init
2021-08-11 Prog.manual update till "new project"
2021-08-12 Handling intern control commands (reset).
2021-08-12 Fixed servo linear movement
2021-08-12 Added buzzer functions
2021-08-12 Fixed servo commands calling. Added command entry autofocus.
2021-08-12 Mechanics manual, cz, revision
2021-08-12 Updated API for LED control. Prog.manual till buttons.
2021-08-12 Electronics manual review
2021-08-12 Added second encoder monitoring.
2021-08-12 Encoder calibration
2021-08-13 Manual electronics cz, review
2021-08-13 Small fixes
2021-08-13 Manual electronics edit
2021-08-13 Updated structure of programming manual.
2021-08-13 First 2 prog. lectures
2021-08-13 More programming lectures
2021-08-14 programming lectures update
    button
2021-08-14 Mechanics manual minor fix
2021-08-14 Fixed encoder threshold setup and calibration
2021-08-14 Fixed encoder threshold storing.
2021-08-15 Changed LED colors and indexes.
2021-08-15 programming lectures update
    added potentiometer
2021-08-15 Potentiometer read in range 0-100.
2021-08-15 Added pictures to programming tutorial
2021-08-16 Electronics manual changes
2021-08-16 Added photo
2021-08-16 Changed Push button index.
2021-08-16 Additional motors controlled. Renamed motors according to silk. Removed track motors speed filter.
2021-08-16 Updated motor api. Converted present sections of prog manual to TJ.
2021-08-17 Prog. tutorial + encoders api.
2021-08-17 Line read and wifi tutorial
2021-08-17 Programming tasks.
2021-08-17 Update lecture 7.
2021-08-17 Shows battery status in web-app
2021-08-17 Added prog_hint.png
2021-08-17 Batt low voltage protection
2021-08-18 Periodic low batt indication
2021-08-18 Battery voltage and info page
2021-08-18 Info Screen Changes
2021-08-18 Prog manual fix
2021-08-18 Battery Status and Voltage merged to one message
2021-08-19 Add play melody option
2021-08-19 Fixed servo indexing. Fixed led manual.
2021-08-19 Added Music Player (Beta)
2021-08-19 Revert "Merge remote-tracking branch 'upstream/main' into main"
    This reverts commit 799921f37bc3124c14d1da9550b28997574ff44a, reversing
    changes made to 96676f5f47c76c1b3b095ec85f2c349d8c1f7739.
2021-08-19 Revert "Revert "Merge remote-tracking branch 'upstream/main' into main""
    This reverts commit 10d234321a322cb9415ec9e53135bcc0bd4bd068.
2021-08-19 Added functions for servo current position and movement.
2021-08-19 Added prog.tasks and updated lectures.
2021-08-20 Some changes
2021-08-20 add bonus tasks to achievements
2021-08-20 Encoder reset function
2021-08-20 Added Non-Blocking PlayMelody
2021-08-20 Added competition.
2021-08-21 Music Player
2021-08-21 Added stopMelody
2021-08-21 Some Fixes
2021-08-21 Added points for competitions.
2021-09-05 Readme text created, minor manual upgrade
2021-09-05 Non-blocking song playing. Status page, refreshing,
2021-12-20 Updated details in manuals, readme.
2021-12-22 Manual sequence in readme
2022-02-08 Fixed prog manual command disp.
2022-10-08 Readme grammatical error fix
2023-02-01 Removed monitor flags from pio.ini
2023-02-01 Added EspExceptionDecoder.
2023-02-03 Fixed platform to espressif32@6.0.0.
